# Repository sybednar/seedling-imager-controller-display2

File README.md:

# Seedling Imager Controller

## Overview
Inspired by the SPIRO (Smart Plate Imaging Robot; Ohlsson et al The Plant Journal doi: 10.1111/tpj.16587) project, the **Seedling Imager** is a Raspberry Pi 5-based imaging system designed to monitor Arabidopsis seedling growth using a 6-position hexagonal carousel. It provides automated imaging, LED control, and experiment scheduling through a touch-friendly GUI.

# Seedling Imager Controller — Universal

**v1.3.0** · Raspberry Pi 5 · PySide6 · picamera2 (or Arducam USB3) · GT2 belt carousel

A touchscreen controller for automated timelapse imaging of seedling plates using near-infrared (940 nm) transmission and front illumination. A single codebase runs on both supported display configurations without any code changes.

Repository: **https://github.com/sybednar/seedling-imager-controller-display2**

---

## Supported Hardware

| Component | System 1 (original) | System 2 |
|---|---|---|
| Display | Original 800×480 DSI touchscreen | Raspberry Pi Touch Display 2 (1280×720) |
| Scale factor `s` | 1.0 | 1.6 |
| Camera | Raspberry Pi HQ Camera | Raspberry Pi HQ Camera |
| Compute | Raspberry Pi 5 | Raspberry Pi 5 |
| Motor | Stepper + GT2 belt carousel | Stepper + GT2 belt carousel |
| Illumination | Dual 940 nm IR LEDs (front + rear) | Dual 940 nm IR LEDs (front + rear) |
| Optical sensor | Photointerrupter (hall + flag) | Photointerrupter (hall + flag) |
| Power (Pi 5) | SZZCNOX 5V/5A PD step-down module | SZZCNOX 5V/5A PD step-down module |

GUI layout, font sizes, button heights, and dialog dimensions all auto-scale via `s = screen_width / 800`. No separate display-specific files are needed.

> **Power supply note:** both systems use the same SZZCNOX 5V/5A USB-PD step-down board. A different-brand step-down module was tried on System 2 during a hardware upgrade and measured **5.42 V** on the Pi 5's 5V rail (GPIO pins 2/4) instead of 5.0 V — that ~0.2 V overvoltage is the confirmed cause of an intermittent shutdown/reboot hang (`plymouth-poweroff`/`plymouth-reboot` stuck for 1–2 minutes, or indefinitely). Swapping back to the SZZCNOX module resolved it completely. **Measure your 5V rail voltage before troubleshooting any shutdown/reboot instability in software** — it will look exactly like an OS or application bug otherwise. See Troubleshooting below.

---

## Key Features (v1.1.0)

### GUI & Display
- Auto-scaling dark theme UI: `s = screen_width / 800` (1.0 at 800 px, 1.6 at 1280 px)
- Fullscreen kiosk mode; all widget dimensions computed as `int(X * s)`
- `dark_style(s)` parameterized stylesheet — font, padding, and border-radius all scale

### Imaging
- Dual 940 nm IR illumination modes: **Front IR**, **Rear IR (transmission)**, **Combined**
- Per-mode camera presets stored in `camera_settings.json` (`FrontIR_*` / `RearIR_*` keys)
- Manual focus locked via `set_manual_focus()` at camera start (measured per unit — see Calibration Notes)
  - PDAF non-functional through 940 nm bandpass filter; manual focus required
- 16-bit grayscale TIFF output (`tifffile`; OpenCV fallback for non-TIFF formats)
- AE stability gate: polls `AnalogueGain` until < 5% relative change over 5 consecutive reads before pinning exposure
- `settling_started` signal emitted **after** AE is pinned and 0.20 s settle — GUI preview snapshot matches saved image exposure
- Live-view IR boost (mode-specific gain/exposure floor) enabled during preview, disabled before capture

### Motor / Carousel
- GT2 belt drive with dynamic bracket homing:
  1. CCW to LOW (leading edge of optical flag)
  2. CCW to HIGH (past leading edge)
  3. CW to LOW (re-validate leading edge)
  4. CW + `mid` µsteps to geometric center
- **Microstepping: 1/32** (BTT TMC2209: MS2=GND, MS1=VCC_IO). `steps_per_60_deg = 3200`.
  - This replaces the earlier 1/8-microstepping configuration (`steps_per_60_deg = 800`). 1/32 microstepping gives substantially finer positioning resolution and improved plate-to-plate registration — see Version History below.
  - **If you are upgrading an existing unit from a lower microstepping setting, delete `motion_cal.json` before the first run** — the saved calibration values do not scale automatically.
- Optical window `W` measured physically each homing run by counting µsteps CW across the sensor aperture (expected W ≈ 192 µsteps at 1/32 microstepping for the 5 mm stripe)
  - W is **not** a configurable parameter — it is measured live every homing cycle
- `CENTER_BACKOFF_FRAC = 0.0`: places carousel at exact geometric center regardless of W
  - Formula: `mid = max(1, int(round(W / 2.0 * (1.0 - CENTER_BACKOFF_FRAC))))`
  - Increase slightly (e.g. 0.05) only if consistent leading-edge drift is observed
- Log output includes `frac=` and `W=` on every homing for traceability

### Camera Backend (Picamera2 / Arducam USB3)
- Selectable in Camera Config → General tab: **Raspberry Pi Camera Module 3 (Picamera2)** [default] or **Arducam 20MP AR2020 Mono USB3**
- Persisted as `CameraBackend` in `camera_settings.json`; **switching requires an application restart** — the backend is fixed for the lifetime of the running process (`camera.py` only imports the selected backend module, since each one claims its physical camera device at import time)
- `camera.py` is a thin dispatcher: every other module calls `camera.get_frame()`, `camera.save_image()`, etc. unchanged regardless of which backend is active
- Arducam backend validated on physical hardware (Sept 2026): full-resolution reopen/discard/retry sequence confirmed reliable across extended multi-cycle experiments, including a `mock_capture()` path that exercises the same reopen sequence for unselected plates so every plate position gets a fresh, reliable on-screen preview whether or not it is actually captured that cycle. Before relying on it for a new unit:
  1. `sudo apt install v4l-utils` (already included in `install_dependencies.sh`)
  2. Connect the camera, then run `python3 -c "import camera_arducam_usb3 as c; c.print_diagnostics()"` — reports the detected `/dev/videoN` device, every resolution/format the driver advertises, and every V4L2 control it exposes
  3. Compare against the assumptions documented at the top of `camera_arducam_usb3.py` (control names, resolutions, mode-switch timing) and adjust the constants there if they don't match
- The Arducam is a **fixed physical manual-focus lens** (twist the M12 ring by hand) — there is no AF motor, so `set_manual_focus()`/AF-related calls are safe no-ops on this backend; the Focus tab in Camera Config has no effect when Arducam is selected
- UVC cameras generally stream one resolution at a time, unlike Picamera2's simultaneous main+lores streams — the Arducam backend runs live preview at a lower resolution continuously and briefly reconfigures to full resolution for each saved image (or each mock capture), so expect a short pause per cycle that the Picamera2 backend does not have

### Germination / Photomorphogenesis LEDs
- Independent on/off toggle buttons for **Blue (450 nm)**, **Red (660 nm)**, and **FarRed (730 nm)** — driven low-side via 3× IRLZ44N MOSFETs on the auxiliary MOSFET board
- Not coupled to the IR imaging illumination cycle — hold any combination on (e.g. Red+FarRed for a red:far-red ratio treatment) while IR imaging continues independently
- State is not persisted between sessions — all three channels default OFF at startup

### Camera Config Dialog
- Tabbed interface: General settings (incl. Camera Backend selector) + Focus + IR-specific presets
- "White LED Front" toggle button (GPIO23, persistent button row next to Apply/Close, not inside the Focus tab so it stays usable for either camera backend) — illuminates a Siemens star target during manual focus calibration; automatically turns off when the dialog closes (Close button, window X, or Escape key)
- Non-blocking "Read Current Position from Camera" button — `_FocusReader(QThread)` worker prevents GUI freeze when Live View is off
- Button disabled during read, re-enabled on completion or error

### Experiment Setup
- Configurable plate selection, frequency (default 30 min), duration, illumination mode
- Disk usage estimate uses `IMAGES_ROOT = Path("/home/sybednar/Seedling_Imager/images")` — **this path is hardcoded in `experiment_setup.py`.** If you use a different Linux username or folder layout, you must edit this line (see Setup, Step 0).
- Storage label colour: green (sufficient free space) / red (insufficient)

### File Manager
- Thumbnail grid with per-image metadata overlay
- Scaled thumbnail size: `QSize(int(100 * s), int(100 * s))`

---

## Module Structure

```
Seedling_Imager/                          # top-level project folder (NOT the git repo)
├── images/                               # timelapse output — IMAGES_ROOT (hardcoded path)
└── seedling_imager_controller/           # git clone of this repository
    ├── venv/                             # Python virtual environment (created locally, not in git)
    ├── main.py                           # Entry point; launches QApplication fullscreen
    ├── gui.py                            # Main window; computes s = screen_width / 800
    ├── styles.py                         # dark_style(s) — parameterized stylesheet
    ├── camera.py                         # Camera BACKEND DISPATCHER — selects picamera2 vs arducam_usb3
    ├── camera_picamera2.py               # Picamera2 backend; manual focus; TIFF save; AE gate
    ├── camera_arducam_usb3.py            # Arducam 20MP AR2020 mono USB3 backend (OpenCV/V4L2)
    ├── camera_config.py                  # Camera Config dialog; Camera Backend selector; _FocusReader QThread
    ├── motor_control.py                  # Stepper driver; dynamic bracket homing; 1/32 microstepping
    ├── experiment_runner.py              # Timelapse loop; AE settle; settling_started signal
    ├── experiment_setup.py               # Setup dialog; plate/frequency/mode/disk usage
    ├── file_manager.py                   # File browser with thumbnail grid
    ├── registration.py                   # Per-plate phase cross-correlation registration analysis
    ├── jog.py                            # Manual motor jog utility for bench testing
    ├── camera_settings.json              # Persisted camera presets (FrontIR_*, RearIR_* keys)
    ├── motion_cal.json                   # Persisted motor calibration (auto-created on first homing)
    ├── requirements.txt                  # pip dependencies (installed inside venv)
    ├── install_dependencies.sh           # One-shot apt + venv + pip installer
    ├── start_seedling_imager.sh          # Launch wrapper used by both autostart methods below
    ├── restart_seedling_imager.sh        # Manual stop/relaunch (used by desktop icon)
    ├── seedling-imager-autostart.desktop # XDG autostart template — RECOMMENDED (see Setup Step 8)
    ├── seedling-imager.service           # systemd --user service template — optional/alternative (see Setup Step 8)
    ├── Seedling_Imager.desktop           # Desktop icon template — start/restart the controller (see Setup Step 9)
    ├── git_update.sh                     # Convenience script for commit + tag + push
    ├── hardware/                         # CAD (STEP), KiCad boards, BOM, render, hardware licence — see hardware/README.md
    ├── logs/                             # Experiment run logs
    └── README.md
```

---

## GPIO Pin Map (as of v1.2.0)

All pins below are on the auxiliary MOSFET board or the motor driver, addressed via `gpiod` against `/dev/gpiochip0`.

| GPIO | Function | Module |
|---|---|---|
| 12 | Germination LED — Blue 450 nm | `gui.py` |
| 13 | Germination LED — Red 660 nm | `gui.py` |
| 16 | Motor DIR | `motor_control.py` |
| 17 | Front IR imaging panel (reflectance) | `gui.py` |
| 19 | Germination LED — FarRed 730 nm | `gui.py` |
| 20 | Motor STEP | `motor_control.py` |
| 21 | Motor driver EN | `motor_control.py` |
| 22 | Optical sensor (reflective stripe) | `motor_control.py` |
| 23 | Front panel White LED strip (Siemens star illumination during manual focus calibration) | `camera_config.py` |
| 24 | Green front illumination | `gui.py` |
| 26 | Hall sensor (motor pre-index) | `motor_control.py` |
| 27 | Rear IR imaging panel (transmission) | `gui.py` |

**v1.2.0 pin reshuffle:** `OPTICAL_PIN` moved 19→22 and the front/rear IR imaging panels moved 13→17 and 12→27, freeing GPIO12/13/19 for the three germination LED channels above. If you're carrying forward calibration or wiring notes from before v1.2.0, update them against this table, not the older pin numbers referenced in earlier Version History entries.

---

## Dependencies

Installed as **apt system packages** (compiled against Raspberry Pi OS's libcamera/Qt6/GPU libraries — do not pip-install these):
```
python3-picamera2
python3-pyside6.*    (no single "python3-pyside6" metapackage on current Raspberry Pi OS/Debian
                       Trixie — PySide6 is split per Qt module; the wildcard installs all of them:
                       sudo apt install 'python3-pyside6.*')
python3-numpy
python3-opencv      (cv2)
v4l-utils           (provides v4l2-ctl — only needed if using the Arducam USB3 camera backend)
libxcb-cursor0      (required by Qt >= 6.5's xcb platform plugin; usually already present, but
                     confirmed missing on at least one fresh Raspberry Pi OS Trixie image — see
                     Troubleshooting)
```

Installed as **pip packages inside the project virtual environment** (see `requirements.txt`):
```
tifffile   (16-bit TIFF read/write)
gpiod>=2.0 (stepper/LED GPIO — modern gpiod.line API; see https://pypi.org/project/gpiod/)
```

> **Note on GPIO library:** this project uses `gpiod` (the modern libgpiod v2.x Python bindings), **not** `RPi.GPIO` and **not** `gpiozero`. Both are absent from the codebase. `gpiod` is installed via pip (not apt) because the apt-packaged `python3-libgpiod` on current Raspberry Pi OS releases may ship an older 1.x API incompatible with `motor_control.py`'s `gpiod.line.Direction/Value/Bias` usage.

The `install_dependencies.sh` script (see Setup below) installs and verifies all of the above in one step.

---

## Setup — New Raspberry Pi 5 (Step by Step for Novices)

These instructions assume you have already flashed Raspberry Pi OS (Bookworm or Trixie) onto the NVMe/SD card, booted to the desktop, confirmed **Desktop Autologin** is enabled for your user (`sudo raspi-config` → System Options → Boot / Autologin → Desktop Autologin), and connected to Wi-Fi/Ethernet. All commands are run in a terminal on the Raspberry Pi itself (or over SSH — except where noted in Step 8/9, where a few things must be checked from a terminal running *inside* the desktop session itself).

### Step 0 — Confirm your Linux username

The code hardcodes the path `/home/sybednar/Seedling_Imager/...` in two places (`experiment_setup.py`'s `IMAGES_ROOT`, and the autostart scripts). Open a terminal and run:

```bash
whoami
```

- If it prints `sybednar`, continue to Step 1 as written.
- If it prints anything else, either (a) create a `sybednar` user on this Pi, or (b) do a project-wide find-and-replace of `/home/sybednar/` with `/home/<your-username>/` in `experiment_setup.py`, `start_seedling_imager.sh`, `restart_seedling_imager.sh`, `seedling-imager.service`, and `seedling-imager-autostart.desktop` before proceeding.

### Step 1 — Create the project folder

```bash
mkdir -p /home/sybednar/Seedling_Imager/images
cd /home/sybednar/Seedling_Imager
```

### Step 2 — Clone the repository

```bash
git clone https://github.com/sybednar/seedling-imager-controller-display2.git seedling_imager_controller
cd seedling_imager_controller
```

(HTTPS clone requires no GitHub account or SSH key setup — fine for read-only cloning of this public repo. If you need the Arducam USB3 branch specifically, add `-b arducam-integration` to the clone command.)

### Step 3 — Install dependencies (one command)

```bash
chmod +x install_dependencies.sh
./install_dependencies.sh
```

This installs the apt system packages, creates `venv/` with `--system-site-packages`, installs `requirements.txt` into it, and prints a verification check for every dependency (picamera2, PySide6, opencv, numpy, tifffile, gpiod). **Do not continue to Step 4 until this script finishes with no errors.**

### Step 4 — Make the launch/restart scripts executable

```bash
chmod +x start_seedling_imager.sh restart_seedling_imager.sh
```

### Step 5 — First manual run (before enabling autostart)

Always test manually first — it's much easier to read errors in a live terminal than in a log file. Run this from a terminal opened **on the Pi's own desktop** (not a bare SSH session), since the app needs the desktop's live display/session environment:

```bash
source venv/bin/activate
python3 main.py
```

The app should open fullscreen. Use Alt+F4 (or the on-screen Exit control, if present) to close it and return to the terminal. If it fails to start, see Troubleshooting below before continuing.

### Step 6 — Calibrate manual focus for this camera unit

Manual focus is **per-camera-unit** and must be re-measured on every new Pi/camera pairing — do not reuse another unit's value. Follow the steps in the repository's `Setting manual camera focus instructions` file, then update the `ManualFocusPosition` value(s) in `camera_settings.json`.

### Step 7 — Confirm the motor calibration file is fresh

If this SSD/OS image was ever used with a different microstepping setting or a different physical unit, delete the stale calibration before the first homing run:

```bash
rm -f /home/sybednar/Seedling_Imager/seedling_imager_controller/motion_cal.json
```

It will be recreated automatically the first time `home()` runs successfully from the GUI.

### Step 8 — Enable autostart (XDG autostart, recommended)

Two mechanisms exist for autostarting the controller GUI when the desktop session starts: a **systemd `--user` service** and an **XDG autostart `.desktop` entry**. Real-world testing across two different Pi 5 units (and, on one of them, two different OS images) consistently found the systemd method **unreliable for this application**: it works fine when started by hand in an already-running session (`systemctl --user enable --now ...`), but on a genuine cold `sudo reboot` it either fails with a Qt platform-plugin error or exits silently a few seconds after launch, with no window ever appearing. The confirmed root cause is that the systemd user manager on these Pi 5 / labwc images does not reliably import `XAUTHORITY`/`WLR_XWAYLAND` into its environment the way an interactive desktop session does — `DISPLAY` and `WAYLAND_DISPLAY` are present, but the xcb/XWayland platform plugin still can't authenticate without those two extra variables. `start_seedling_imager.sh` already sets explicit fallback defaults for both (see the script), which helps but has not made systemd fully reliable across every image tested. The **XDG autostart** method sidesteps the problem entirely, since the compositor launches it directly inside the already-fully-initialized session — it has been 100% reliable across every reboot/shutdown test performed. **Use it as the primary method:**

```bash
mkdir -p ~/.config/autostart
cp seedling-imager-autostart.desktop ~/.config/autostart/seedling-imager.desktop
```

**Reboot the Pi with `sudo reboot` (a real reboot — not `systemctl --user start`) and confirm the controller launches automatically to the fullscreen GUI.** Also test a full `sudo shutdown now` to confirm the Pi actually powers off cleanly. Testing only with a live-session start can look successful and still fail on a real cold boot — always validate with an actual reboot and an actual shutdown before considering autostart done.

If the GUI doesn't appear, check the log first:

```bash
tail -80 /home/sybednar/Seedling_Imager/seedling_imager_controller/autostart.log
```

<details>
<summary>Optional: systemd <code>--user</code> service (alternative method — click to expand)</summary>

If you'd prefer process supervision (automatic restart on crash) and are willing to validate it carefully, the systemd unit is still provided:

```bash
mkdir -p ~/.config/systemd/user
cp seedling-imager.service ~/.config/systemd/user/
systemctl --user daemon-reload
systemctl --user enable --now seedling-imager.service
```

Check it's running:

```bash
systemctl --user status seedling-imager.service --no-pager -l
```

**Do not stop here** — this only confirms it works when started inside your current live session, which is exactly the false-positive result seen on both test units before a real reboot exposed the failure. Reboot and re-check status/log before trusting it:

```bash
sudo reboot
# after it comes back up:
systemctl --user status seedling-imager.service --no-pager -l
tail -80 /home/sybednar/Seedling_Imager/seedling_imager_controller/autostart.log
```

If it fails (Qt platform-plugin error, or the log shows the script exiting cleanly within a few seconds of launch with no other error), fall back to the XDG method above:

```bash
systemctl --user disable --now seedling-imager.service
mkdir -p ~/.config/autostart
cp seedling-imager-autostart.desktop ~/.config/autostart/seedling-imager.desktop
sudo reboot
```

</details>

### Step 9 — Add the "Seedling Imager" desktop icon

This lets you start (or stop-and-relaunch) the controller from the touchscreen — e.g. after using "Exit to Desktop" to review files — without rebooting the Pi.

```bash
cp Seedling_Imager.desktop ~/Desktop/
chmod +x ~/Desktop/Seedling_Imager.desktop
```

**Two one-time desktop settings, or the icon won't work smoothly:**

1. On first double-click, the file manager may show an "Untrusted application launcher" warning — right-click the icon and choose **Allow Launching** (or **Trust**), then it will run normally from then on.
2. By default, clicking an executable `.desktop`/script icon pops up an "Execute / Execute in Terminal / Display / Cancel" dialog every time instead of just running it. To disable this: open the **File Manager**, go to **Edit → Preferences** (or right-click the desktop → **Desktop Preferences**, depending on OS version), find the **General** tab, and check **"Don't ask options on launch executable file."** Without this, every click on the icon interrupts the user with an extra dialog.

The icon uses `seedlings.png` (already in this repo) and calls `restart_seedling_imager.sh`, which kills any already-running instance of the GUI and relaunches `start_seedling_imager.sh` fresh — safe to click whether or not the controller is currently running.

### Step 10 — Run a short registration test

Run a short multi-cycle experiment (a few plates, a few cycles) and inspect results with `registration.py` to confirm the 1/32-microstepping `motor_control.py` gives the same registration improvement seen on System 1 before starting a long unattended run.

---

## Troubleshooting

| Symptom | Likely cause / fix |
|---|---|
| `pip install` fails with "externally-managed-environment" | You're not inside the venv, or the venv was created without `--system-site-packages`. Re-run `source venv/bin/activate` first, or rebuild the venv per Step 3. |
| `ModuleNotFoundError: No module named 'picamera2'` inside the venv | The venv wasn't created with `--system-site-packages`, or the apt package `python3-picamera2` isn't installed. Rebuild: `rm -rf venv && python3 -m venv --system-site-packages venv`, then re-run `install_dependencies.sh`. |
| `ImportError: cannot import name 'Direction' from 'gpiod.line'` | An old `gpiod` (1.x) is shadowing the pip-installed 2.x version. Confirm with `venv/bin/pip show gpiod` (should be ≥2.0) and re-run `venv/bin/pip install --upgrade gpiod`. |
| `qt.qpa.plugin: Could not load the Qt platform plugin "xcb" ... xcb-cursor0 or libxcb-cursor0 is needed` | Missing system library required by Qt ≥ 6.5. Fix: `sudo apt-get install -y libxcb-cursor0`. Seen on a fresh Raspberry Pi OS Trixie image where it wasn't pulled in automatically. |
| `qt.qpa.xcb: could not connect to display` when testing manually | You're running the command over plain SSH (no `DISPLAY`), not in a terminal inside the desktop session. Either open a terminal locally on the Pi's touchscreen, or (for a quick manual check only) `export DISPLAY=:0` in the SSH shell first. |
| GUI never appears at boot, but manual `python3 main.py` (run inside the desktop session) works fine | This is the systemd `XAUTHORITY`/`WLR_XWAYLAND` gap described in Setup Step 8. Switch to the XDG autostart method — don't spend time tuning `QT_QPA_PLATFORM` or startup delay first, since neither addresses the actual cause. |
| systemd service shows `enabled`, `autostart.log` shows the script reach `Seedling Imager launch end` a few seconds after launch, but no window ever appeared | The app started and exited cleanly on its own under systemd — a different, not-fully-understood failure mode from the Qt platform-plugin error above, also resolved by switching to XDG autostart. Confirmed independent of camera backend and hardware revision. |
| systemd service works when started by hand (`enable --now`) but not after a real `sudo reboot` | Expected — see Setup Step 8. Validate autostart only with a genuine reboot, never with a live-session start. |
| `sudo shutdown`/`sudo reboot` hangs for 1–2 minutes (or indefinitely) at a `plymouth-poweroff`/`plymouth-reboot` message | Check your Pi 5's 5V rail voltage (GPIO pins 2/4) before assuming it's a software issue — a step-down power module running even slightly over 5.0 V (5.4 V confirmed to cause this) can produce exactly this symptom. See the Power Supply note near the top of this README. Also run `sudo rpi-eeprom-update` and apply any pending bootloader update (`sudo rpi-eeprom-update -a && sudo reboot`) as a secondary check, especially on units with an NVMe HAT. A momentary pushbutton wired to the J2 GPIO shutdown pins will reliably force a clean power-down while you diagnose this. |
| Clicking the desktop icon pops up an Execute/Terminal/Cancel dialog every time | See Setup Step 9 — enable "Don't ask options on launch executable file" in the File Manager's preferences. |
| Homing/centering seems off after this update | Delete `motion_cal.json` and re-home — old calibration values from a different microstepping setting do not carry over (see Motor / Carousel notes above). |

---

## Migrating an Existing Unit to This Layout

If a unit's folder/autostart layout predates this document, bringing it in line is usually a small job, not a rebuild:

1. **Confirm the folder structure first before assuming anything needs to move.** Check `ls -la /home/<user>/Seedling_Imager/` and `ls -la /home/<user>/Seedling_Imager/seedling_imager_controller/venv/bin/python3` — many units already have the correct layout (repo cloned into `Seedling_Imager/seedling_imager_controller/`, venv nested inside it) even if that wasn't true at some earlier point in the unit's history. Don't move files that are already in the right place.
2. **The autostart mechanism is the part most likely to need changing.** If the unit currently relies on the systemd `--user` service, convert it to the XDG autostart method per Setup Step 8 — do this even if the systemd version currently "seems to work," since a live-session start can pass while a real cold reboot fails (see Troubleshooting). Validate with an actual `sudo reboot` and `sudo shutdown`, not just `systemctl --user enable --now`.
3. Update the desktop icon to the current `Seedling_Imager.desktop` template and confirm the File Manager preference from Setup Step 9 is set.
4. Back up (rename, don't delete) any old/stale project folders before removing them, and only delete the backups once the converted unit has been confirmed working across a real reboot and shutdown.
5. **Do not touch a unit while it is running an experiment.** Do this migration between experimental runs.

---

## Calibration Notes

### Manual Focus
- Manual focus is per-camera-unit. Measure and set `ManualFocusPosition` in `camera_settings.json` for each new system — do not copy another system's value.
- PDAF is non-functional through the 940 nm bandpass filter on both systems.

### Optical Window W
W is measured automatically on every homing cycle — no manual configuration needed. Expect W ≈ 192 µsteps at 1/32 microstepping for the 5 mm stripe.

### CENTER_BACKOFF_FRAC
At the top of `motor_control.py`. Default `0.0` places the carousel at exact geometric window center. Only increase if consistent leading-edge drift is observed in registration analysis.

---

## Hardware Design Files

The complete open-source hardware design is in [`hardware/`](hardware/README.md): the full assembly and individual parts in STEP format, KiCad 10 schematics and PCB layouts for the controller boards and hall sensor board, and a bill of materials (`hardware/CAD Files/bill_of_materials.md`). The native Fusion archive (`.f3z`) and full-assembly STEP are too large for the repository and are attached to the [latest GitHub Release](https://github.com/sybednar/seedling-imager-controller-display2/releases/latest). Hardware files are licensed under CERN-OHL-S v2; the software is MIT.

---

## Version History

### v1.3.2 — 2026-10-04 — Hardware documentation and naming corrections

- Renamed the IR filter holder component to "850 nm long-pass filter holder" in the CAD (Fusion archive and all STEP files)
- Clarified that the camera housing, filter holder and rail corner bracket are included in the Picamera mount STEP; updated root README, CHANGELOG and citation
- Software unchanged from v1.3.0

### v1.3.1 — 2026-10-04 — Complete hardware design files

- Added the complete hardware design (`hardware/`): full-assembly STEP (zipped) and individual part STEP files by subsystem, KiCad 10 files for controller board 1, board 2 and the hall sensor board, bill of materials, assembly render, and CERN-OHL-S v2 licence/notice
- Fusion archive (`.f3z`) and full-assembly STEP attached to the GitHub Release (files exceed GitHub's 100 MB repository limit)
- Added root `LICENSE` (MIT) for the software
- Software unchanged from v1.3.0

### v1.3.0 — 2026-09-27 — Arducam reliability fixes, White LED Front control, Picamera2 for production

**Reliability fixes**
- Fixed `focus_tune.py` sharpness score: removed per-frame min/max contrast normalization that was causing the reported score to rise with *increasing* defocus instead of decreasing
- Fixed Arducam USB3 single-capture failure (root-caused via `dmesg`: `uvcvideo: Failed to resubmit video URB`, a genuine kernel-level USB/firmware wedge triggered by rapid full-res/preview mode switching) — added a settle delay before reopening the device plus self-healing device re-detection (`_find_device(force_refresh=True)`)

**New hardware control**
- Added a "White LED Front" toggle button (GPIO23) to the Camera Config dialog, placed in the persistent button row so it stays usable regardless of active tab or selected backend. Illuminates a Siemens star target for manual focus calibration on either camera; auto-shuts-off via the dialog's `finished` signal so it turns off no matter how the dialog is closed
- Corrected GPIO Pin Map: GPIO23 and GPIO24 were previously documented as "reserved, not yet implemented" — GPIO24 was already driving the Green front illumination LED (`gui.py`), and GPIO23 now drives the White LED Front strip above, both via the AO4805 MOSFET auxiliary board

**Hardware/production decision**
- Head-to-head image-quality comparison on both systems (focus, depth of field, sharpness) showed Picamera2/Camera Module 3 substantially outperforming the Arducam 20MP AR2020 Mono + AICO M12 lens combination for real seedling-plate imaging, after root-causing the Arducam's low sharpness ceiling to a Minimum-Object-Distance violation (measured working distance below the lens's MOD). Both systems switched to Picamera2 for production experiments; the Arducam lens/working-distance problem is tabled for future revisit — the backend and its fixes above remain in the codebase and selectable via Camera Config

**Repo maintenance**
- Consolidated system 1 onto `origin/main`, resolving stale branch/merge-conflict history
- Fixed GitHub default branch (was pointing to the archived `archive-pre-arducam-2026-04` branch instead of `main`); deleted stale `arducam-integration` and `archive-pre-arducam-2026-04` branches and the leftover local `main-old-stale`

### v1.2.1 — 2026-09 — Autostart reliability fix + setup documentation overhaul

**Autostart**
- Root-caused systemd `--user` autostart unreliability to `XAUTHORITY`/`WLR_XWAYLAND` not being reliably imported into the systemd user manager's environment on Pi 5/labwc images, even though `DISPLAY`/`WAYLAND_DISPLAY` are present. `start_seedling_imager.sh` now sets explicit fallback defaults for both.
- XDG autostart (`~/.config/autostart/`) promoted to the **recommended** primary method after passing repeated real cold-reboot and full-shutdown testing on two separate physical units; systemd retained as a documented, secondary/optional method.
- Desktop icon renamed/consolidated to a single `Seedling_Imager.desktop` template (start-or-restart), replacing the earlier restart-only icon naming.

**Hardware**
- Documented a confirmed root cause for intermittent `plymouth-poweroff`/`plymouth-reboot` shutdown hangs: a non-matching 5V step-down power module running at 5.42 V instead of 5.0 V. Resolved by standardizing on the SZZCNOX 5V/5A module on both systems.
- Added `sudo rpi-eeprom-update` as a secondary shutdown-instability check, particularly for units with an NVMe HAT.

**Camera**
- Arducam USB3 backend validated against physical hardware across extended multi-cycle runs; added `mock_capture()` so every plate position gets a fresh, reliable on-screen preview regardless of whether that plate is actually captured that cycle.

**Dependencies**
- Added `libxcb-cursor0` as a documented apt dependency (Qt ≥ 6.5 requirement, found missing on a fresh Raspberry Pi OS Trixie image).

### v1.2.0 — 2026-08 — Selectable camera backend, germination LEDs, GPIO reshuffle

**Camera**
- `camera.py` split into a backend dispatcher plus two implementations: `camera_picamera2.py` (existing Picamera2/libcamera code, behavior unchanged) and new `camera_arducam_usb3.py` (OpenCV/V4L2 backend for the Arducam 20MP AR2020 monochrome USB3 camera)
- Backend selectable in Camera Config → General (`CameraBackend` in `camera_settings.json`); requires an app restart to take effect

**Hardware / GPIO**
- Added a 3-channel germination/photomorphogenesis LED strip (Blue 450 nm, Red 660 nm, FarRed 730 nm) with independent GUI on/off toggles, driven low-side via IRLZ44N MOSFETs on a new auxiliary MOSFET board
- Reshuffled GPIO pins to make room: `motor_control.py`'s `OPTICAL_PIN` moved 19→22; `gui.py`'s front/rear IR imaging panel pins moved 13→17 and 12→27. See the GPIO Pin Map above for the full current assignment, including GPIO23/24 reserved for a planned rear-IR940 PWM intensity control (AO4805 mosfet, not yet implemented in software)

**Dependencies**
- Added `v4l-utils` (apt) for the Arducam backend's `v4l2-ctl`-based exposure/gain control

### v1.1.0 — 2026-07 — 1/32 microstepping + documentation overhaul

**Motor**
- `motor_control.py` updated from 1/8 to 1/32 microstepping (`steps_per_60_deg`: 800 → 3200), same single-optical-sensor + 6-stripe dynamic-bracket strategy. Finer step resolution further improves plate-to-plate registration.
- Cleaned a leftover dead-code block in `_debounced_read()`.

**Documentation**
- Corrected GPIO dependency: `RPi.GPIO`/`gpiozero` (never used in code) replaced with `gpiod>=2.0` throughout.
- Replaced three conflicting clone/folder-structure instructions with a single canonical layout and step-by-step novice setup guide.
- Added `requirements.txt`, `install_dependencies.sh`, systemd service template, XDG autostart fallback template, and desktop restart-icon template — previously undocumented/uncommitted.
- Fixed repository URL (previous README referenced two nonexistent repo names).

### v1.0.0 — 2026-04-22 — Universal release

**Architecture**
- Single codebase runs on both 800×480 and 1280×720 displays without modification
- `s = screen_width / 800` computed once in `gui.py`; every pixel dimension expressed as `int(X * s)`
- `dark_style(s)` replaces fixed stylesheet string; font, padding, border-radius all scale with `s`

**Motor / centering fix**
- `CENTER_BACKOFF_FRAC = 0.0` replaces fixed `CENTER_BACKOFF = 5`
- Fixes System 1 centering error: with W=12 the old formula gave `mid=1` (leading edge) instead of `mid=6` (center)
- After pulley realignment: W=23–24, mid=12; registration RMS improved ~79% (6.7 px → 1.4 px mean)

**Imaging**
- AE stability gate: waits for AnalogueGain < 5% relative change × 5 consecutive reads before pinning exposure
- `settling_started` signal timing fixed: now emitted after AE pin + 0.20 s settle, not before — preview snapshot matches saved image exposure
- Non-blocking Read Focus button: `_FocusReader(QThread)` prevents GUI freeze when Live View is off

**Bug fixes**
- `IMAGES_ROOT` constant added to `experiment_setup.py` (was causing silent disk estimate failure)
- Experiment frequency default restored to 30 minutes
- `apply_main_illum_style` scope fix: `s = self._s` added inside method body
- `experiment_setup.py` line 235: orphaned `else` clause fixed (comment had been inserted between `if` body and `else`)
- `gui.py`: `setStyleSheet(dark_style(s))` moved to after `s` is computed (was causing `UnboundLocalError`)

**All v0.06 Display2 features carried forward**
- Dual 940 nm IR illumination (front + rear), per-mode camera presets
- Tabbed Camera Config dialog, File Manager with thumbnails, CSV metadata
- GT2 belt drive, autostart and desktop launcher

### v0.06 — Display2-specific release
Dual-stream camera, TIFF output, autofocus, File Manager with thumbnails, CSV metadata, Camera Config dialog, autostart and desktop launcher, GT2 belt drive initial implementation, per-mode IR presets.

---

## Registration Performance (System 1, v1.0.0, 1/8 microstepping baseline)

Rear IR transmission, 8 cycles, plates 1 and 2:

| Metric | v0.06 baseline | v1.0.0 |
|---|---|---|
| Mean RMS | 6.7 px | 1.4 px |
| Mean \|dx\| | 6.5 px | 1.3 px |
| dx bias | +6.5 px (systematic) | −0.4 px (eliminated) |
| Cycles at 0 px shift | 0 of 4 | 9 of 14 (64%) |
| Max \|dx\| | 10 px | 6 px |

Residual jitter (2–6 px) is intrinsic GT2 belt backlash and stepper microstepping nonlinearity. Software registration using ArUco or QR fiducial markers on plate backs can correct remaining shift to sub-pixel if required for quantitative analysis. **1/32-microstepping results from System 2 will be added here once validated (see Setup Step 10).**

---

## License

Software: MIT — see `LICENSE` file. Hardware design files (`hardware/`): CERN-OHL-S v2 — see `hardware/LICENSE-CERN-OHL-S-v2.txt`.

Citation: Bednarek, S. Y., Yong, C. W. J., Hoey, E. A. and Murua, K. (2026). *seedling-imager-controller-display2* (v1.3.2). Zenodo. https://doi.org/10.5281/zenodo.23144486 (all versions: https://doi.org/10.5281/zenodo.20738657).

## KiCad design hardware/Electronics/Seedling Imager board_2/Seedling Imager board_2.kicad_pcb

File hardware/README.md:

# Seedling Imager — Hardware Design Files

Open-source hardware for an automated, six-plate time-lapse seedling imaging robot.
This folder contains the mechanical CAD files, controller electronics (KiCad), bill of
materials, and licensing for the imager; the Raspberry Pi controller and
image-acquisition/registration software live in the root of this repository.

## Overview

The instrument is a rotating hexagonal carousel that holds up to six Petri plates and
presents each in turn to a fixed high-resolution camera. It is controlled by a
Raspberry Pi with a stepper motor and optical/magnetic position sensors, so every plate
returns to the same imaging position on each cycle. Plates are illuminated with both
transmitted and reflected 940 nm infrared light, allowing seedlings to be grown and
imaged either in the light or in complete darkness (etiolated), typically at 1–2 hour
intervals over 5–7 days. The system captures 16-bit grayscale TIFF images and
automatically aligns successive frames of each plate by phase cross-correlation
(frame-to-frame registration to ~2 pixels in current data).

The design was inspired by the open-source SPIRO Petri-plate imaging robot
(Ohlsson et al., 2024, *The Plant Journal* 118:584–600) and extends it with greater
plate capacity, dual transmitted + reflected IR illumination, and improved registration
reproducibility for quantitative time-lapse growth analysis.

## Contents

| Path | Description |
|------|-------------|
| `seedling imager_full assembly.step.zip` | Complete assembly in neutral STEP format (zipped; unzip before opening). Opens in any CAD package (FreeCAD, SolidWorks, Onshape, etc.). |
| Fusion archive `seedling imager_full assembly.f3z` | Native Autodesk Fusion archive of the complete assembly (127 MB, too large for the repository). Download from the **[latest GitHub Release](https://github.com/sybednar/seedling-imager-controller-display2/releases/latest)** and open in Fusion. |
| `CAD Files/` | Individual part and sub-assembly STEP files, organized by subsystem (below), plus `bill_of_materials.md`. |
| `Electronics/` | KiCad 10 schematic and PCB design files for the controller boards and hall sensor board (below). |
| `LICENSE-CERN-OHL-S-v2.txt` | Hardware license (see Licensing). |
| `NOTICE.txt` | Required CERN-OHL-S copyright/license notice. |

### CAD Files/ (STEP format, by subsystem)

| Folder | Contents |
|--------|----------|
| `Drive Base and Frame/` | Base plate, top plate, motor tensioning plate |
| `Carousel Assembly/` | Six-plate carousel with dual-bearing belt drive, carousel support bracket, adjustable bearing arms (including the optical sensor mount and the hall sensor arm), acrylic plate diffuser, the dual bearing belt drive motor base block, and the magnet and optical carousel position sensor triggers |
| `Rear Illuminator/` | Rear IR/illumination support hub |
| `Camera and Controller Mount/` | Display/camera rail light screen mounting hub assembly; Picamera mount with CSI-to-HDMI board (includes the camera housing, IR long-pass filter holder and rail corner bracket) |
| `Controller Enclosure/` | Display/touchscreen controller enclosure assembly (hinge, touchscreen compartment, RPi compartment, rear panel) |
| `Controller Subassembly/` | 3D models of the custom controller boards (Seedling Imager board_1 and board_2) |
| `Miscellaneous Hardware/` | 2020 T-slot end cap with cover, 2020 T-slot cover wire guide, 2020 8 mm cable guide, 100 mm × 15 mm square Petri dish magnetic fastener (8 mm magnet), M5 thumb screws (15 mm and 25 mm), Meanwell LRS-100-12 power supply enclosure, corner bracket, and fabrication jigs (acrylic diffuser hole-drilling jig, spindle heat-set insert installation jig) |

Standard off-the-shelf hardware (fasteners, 2020 aluminum extrusion, stepper motor, etc.)
is not included as CAD files — see `CAD Files/bill_of_materials.md` for part numbers.

### Electronics/ (KiCad 10)

| Folder | Description |
|--------|-------------|
| `Seedling Imager board_1/` | Main controller board (TMC2209 stepper driver, LED and sensor interfaces). Includes the `TSW_103_07_L_S` library (symbol, footprint and 3D model for the 0.1" pitch header). |
| `Seedling Imager board_2/` | Auxiliary MOSFET board for LED illumination control. |
| `Seedling Imager hall sensor board/` | A3144 hall sensor board mounted in the adjustable bearing arm for magnetic carousel position sensing. |

Each folder holds the `.kicad_pro`, `.kicad_sch` and `.kicad_pcb` files; open the
`.kicad_pro` in KiCad 10 or later. Schematic symbols and PCB footprints are embedded in
the files, so the boards open without extra libraries. Some PCB files reference 3D
models by absolute path on the author's machine; these only affect the 3D viewer and can
be re-pointed in *PCB Editor ▸ Preferences ▸ Configure Paths* or by editing footprint
properties.

## Opening the design files

- **STEP (.step):** Unzip `seedling imager_full assembly.step.zip`, then open the `.step`
  in any CAD program. STEP preserves exact solid geometry and is the recommended
  starting point for reuse or modification outside Fusion. The individual `.step` files
  in `CAD Files/` can be opened directly.
- **Fusion archive (.f3z):** Download it from the latest GitHub Release, then in Autodesk Fusion use *File ▸ Open* and select the `.f3z`,
  or upload it to your Fusion data panel. This is the fully editable source design
  (Fusion is free for personal/hobbyist use).

## Bill of materials

See `CAD Files/bill_of_materials.md`, grouped by category (structural and motion
components, electronics, power, motor, lights, wiring, hardware, ArUco markers, 2020
extrusion cut list, camera housing hardware, and controller board connectors).

## Notes

- An alternate camera/lens configuration (Arducam 20 MP monochrome + Computar M0814-MP2
  C-mount lens) was evaluated but has not yet been built or tested. Its CAD files are not
  included; the Picamera system above is the one running production experiments.
- The camera housing/mount, the IR long-pass filter holder (for the 37 mm 850 nm filter) and the
  mounting rail corner bracket are modeled as components of
  `Camera and Controller Mount/picamera mount_with csi to hdmi board.step` (and of the full
  assembly) rather than as separate files.

## Build and operation

Controller setup, camera configuration, and operation: see the documentation in the
repository root (`README.md`, `Camera configuration_user guide`,
`Setting manual camera focus instructions`).

## Licensing

This project uses two licenses:

- **Hardware design files** (CAD, STEP, KiCad, BOM) in this folder are licensed under the
  **CERN Open Hardware Licence Version 2 — Strongly Reciprocal (CERN-OHL-S v2)**.
  See `LICENSE-CERN-OHL-S-v2.txt` and `NOTICE.txt`.
- **Software** (the Raspberry Pi controller and image-acquisition/registration code) in
  the repository root is licensed under the **MIT** license.
  See the `LICENSE` file at the repository root.

## Citation

If you use this hardware or software, please cite the archived release:

> Bednarek, S. Y., Yong, C. W. J., Hoey, E. A. and Murua, K. (2026). *seedling-imager-controller-display2: control and image-acquisition
> software and hardware design files for an open-source six-plate infrared seedling imaging
> robot* (v1.3.2) [Software and hardware design files]. Zenodo. https://doi.org/10.5281/zenodo.23144486
>
> The DOI above is for release v1.3.2. To cite all versions (always resolves to the latest
> release), use https://doi.org/10.5281/zenodo.20738657.

## Contact

Sebastian Y. Bednarek, University of Wisconsin–Madison — sybednar@wisc.edu

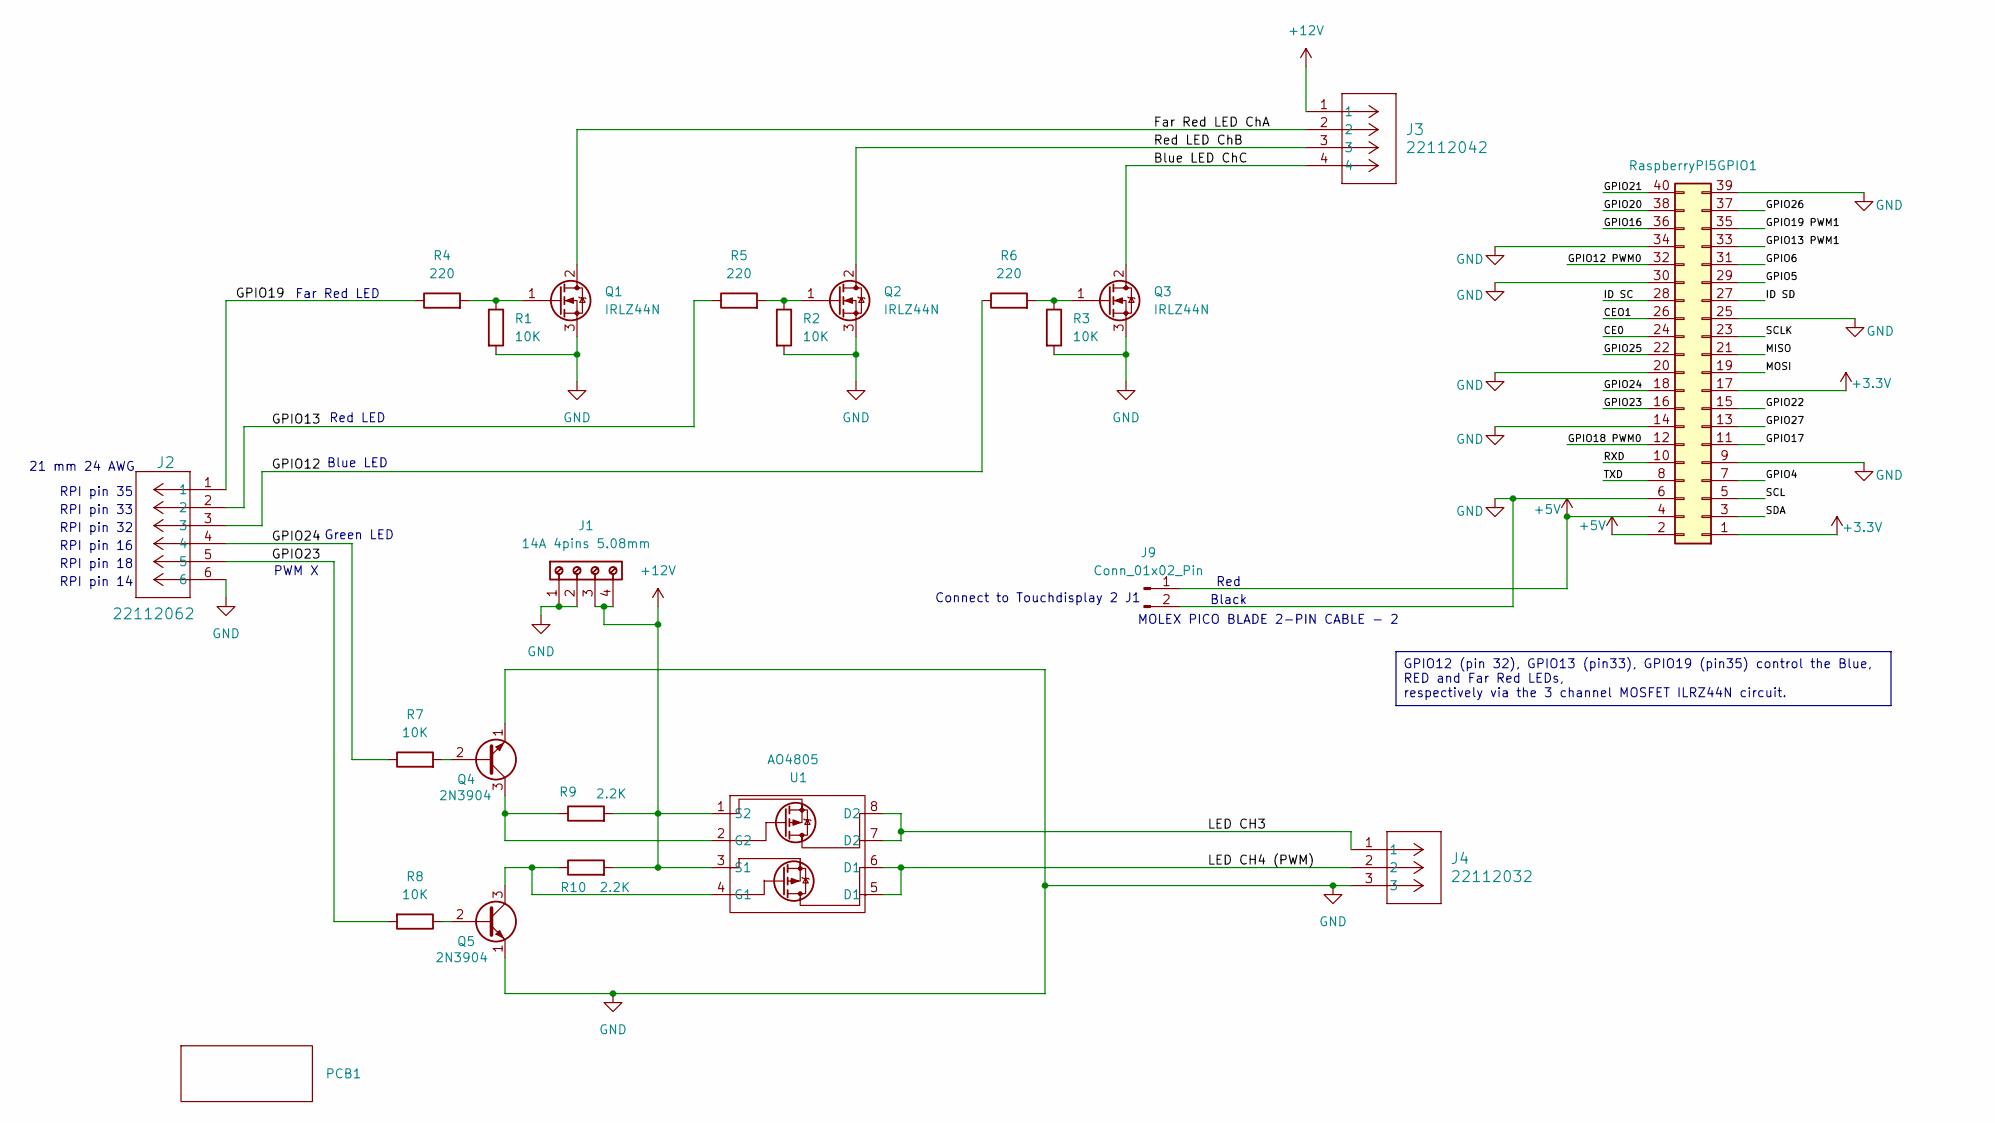
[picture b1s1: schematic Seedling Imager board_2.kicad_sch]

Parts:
J1: 691241510004; J_Wurth_WR-TBL_691241510004; Part Number 691241510004
J2: 22112062; CONN_A-6373-06A_MOL
J3: 22112042; CONN_A-6373-04A_MOL
J4: 22112032; CONN_A-6373-03A_MOL
J9: Conn_01x02_Pin
PCB1: DMB-4770-CB_cut
Q1, Q2, Q3: IRLZ44N; TO-220-3_Vertical
Q4, Q5: 2N3904; TO-92_Inline_Wide
R1, R2, R3, R7, R8: 10K; R_Axial_DIN0204_L3.6mm_D1.6mm_P5.08mm_Horizontal
R4, R5, R6: 220; R_Axial_DIN0204_L3.6mm_D1.6mm_P5.08mm_Horizontal
R9, R10: 2.2K; R_Axial_DIN0204_L3.6mm_D1.6mm_P5.08mm_Horizontal
RaspberryPI5GPIO1: Conn_02x20_Odd_Even; RHDR40W60P250_2X20_5100X500X23
U1: AO4805; SOIC127P600X175-8N

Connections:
+12V: J1.3, J1.4, J3.1, R9.2, R10.2, U1.1 (S2), U1.3 (S1)
/Blue LED ChC: J3.4, Q3.2 (D)
/Far Red LED ChA: J3.2, Q1.2 (D)
/GPIO12: J2.3, R6.1
/GPIO13: J2.2, R5.1
/GPIO19: J2.1, R4.1
/GPIO23: J2.4, R7.1, RaspberryPI5GPIO1.18
/GPIO24: J2.5, R8.2, RaspberryPI5GPIO1.16
/LED CH3: J4.1, U1.7 (D2), U1.8 (D2)
/LED CH4 (PWM): J4.2, U1.5 (D1), U1.6 (D1)
/Red LED ChB: J3.3, Q2.2 (D)
GND: J1.1, J1.2, J2.6, J4.3, J9.2, Q1.3 (S), Q2.3 (S), Q3.3 (S), Q4.1 (E), Q5.1 (E), R1.2, R2.2, R3.2, RaspberryPI5GPIO1.6, RaspberryPI5GPIO1.9, RaspberryPI5GPIO1.14, RaspberryPI5GPIO1.20, RaspberryPI5GPIO1.25, RaspberryPI5GPIO1.30, RaspberryPI5GPIO1.34, RaspberryPI5GPIO1.39
unnamed: J9.1, RaspberryPI5GPIO1.2, RaspberryPI5GPIO1.4
unnamed: Q1.1 (G), R1.1, R4.2
unnamed: Q2.1 (G), R2.1, R5.2
unnamed: Q3.1 (G), R3.1, R6.2
unnamed: Q4.2 (B), R7.2
unnamed: Q4.3 (C), R9.1, U1.2 (G2)
unnamed: Q5.2 (B), R8.1
unnamed: Q5.3 (C), R10.1, U1.4 (G1)
unnamed: RaspberryPI5GPIO1.1, RaspberryPI5GPIO1.17

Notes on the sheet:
Connect to Touchdisplay 2 J1
RPI pin 16
RPI pin 33
PWM X
Black
Blue LED
RPI pin 18
21 mm 24 AWG
RPI pin 35
RPI pin 32
Red LED
MOLEX PICO BLADE 2-PIN CABLE - 2
RPI pin 14
Far Red LED
Green LED
Red
GPIO12 (pin 32), GPIO13 (pin33), GPIO19 (pin35) control the Blue, RED and Far Red LEDs, respectively via the 3 channel MOSFET ILRZ44N circuit.

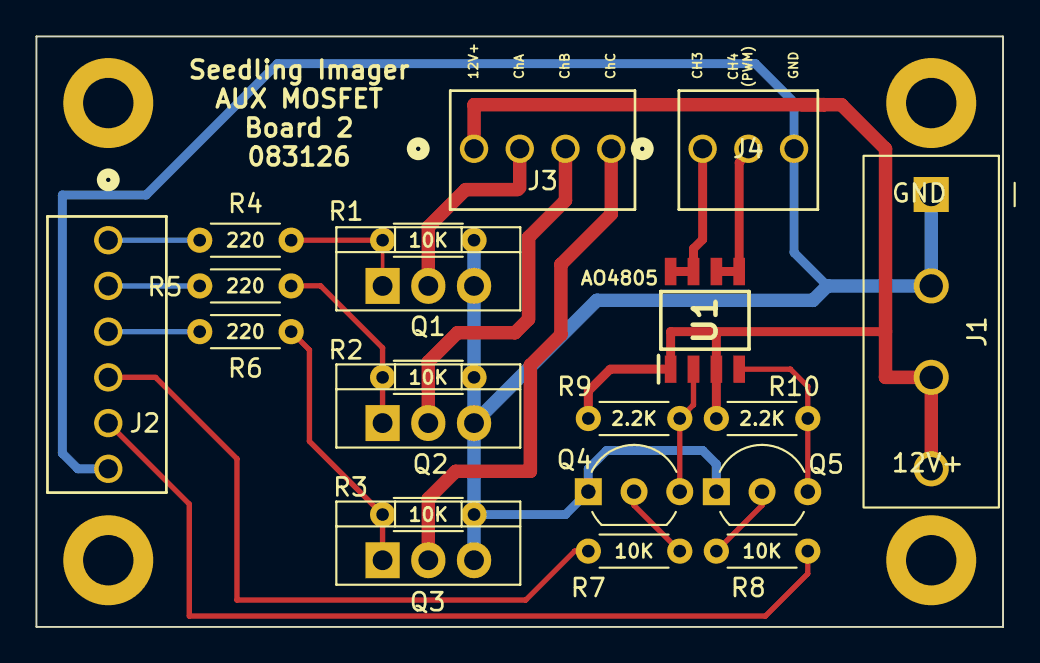
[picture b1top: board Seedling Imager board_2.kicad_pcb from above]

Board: 2 copper layers, 53.7 x 32.8 mm, 21 parts (0 on the bottom side), 19 nets.

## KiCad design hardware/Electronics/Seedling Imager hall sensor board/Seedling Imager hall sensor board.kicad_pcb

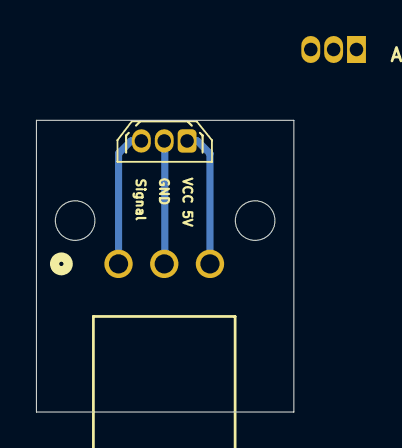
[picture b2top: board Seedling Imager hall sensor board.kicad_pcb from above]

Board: 2 copper layers, 14.3 x 16.2 mm, 5 parts (0 on the bottom side), 3 nets.

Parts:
A3144: A1104xLH; TO-92L_Inline
H1, H2: MountingHole; MountingHole_2.2mm_M2
J1: 22053031; CONN_A-7478-03A_MOL
U1: A3144; TO-92Flat

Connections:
/GND: J1.2, U1.2 (GND)
/Signal: J1.1, U1.3 (SIGNAL)
/VCC 5V: J1.3, U1.1 (V_{CC})

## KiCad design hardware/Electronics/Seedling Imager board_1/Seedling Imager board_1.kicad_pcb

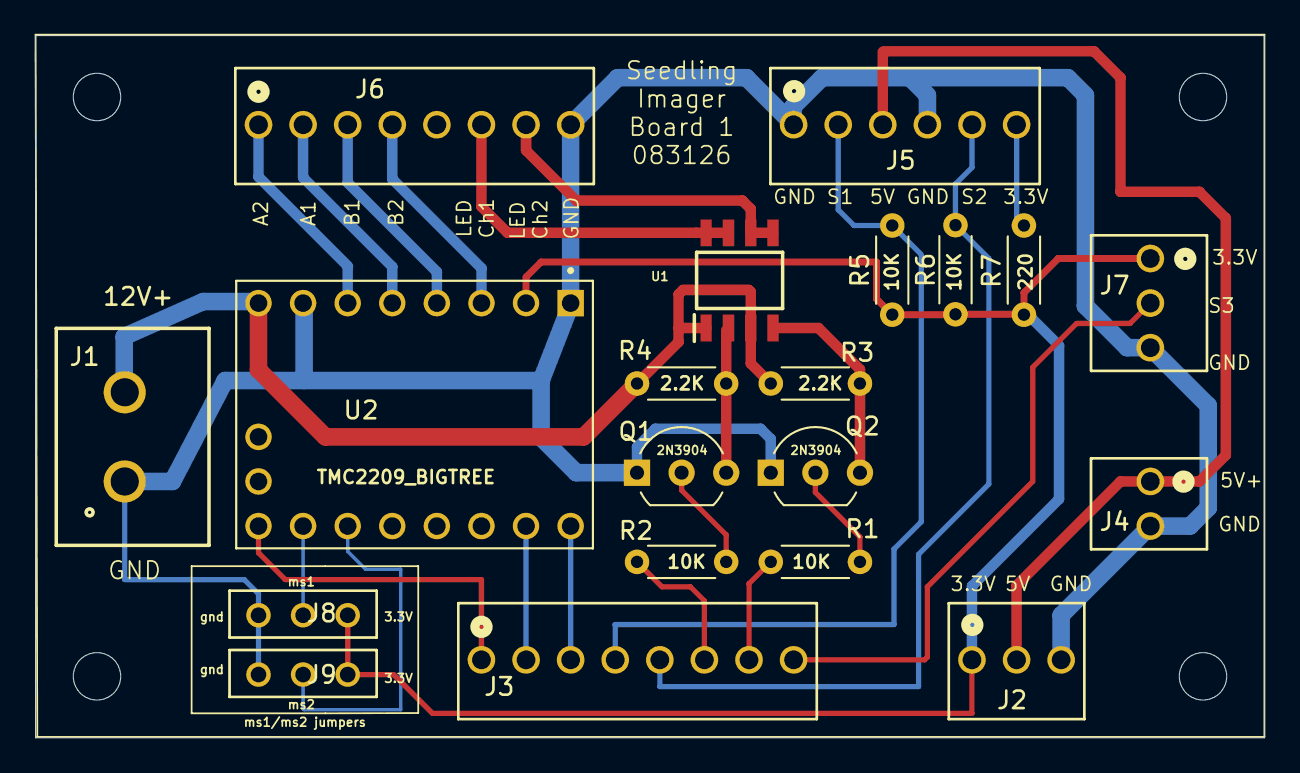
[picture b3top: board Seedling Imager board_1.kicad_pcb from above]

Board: 2 copper layers, 70.0 x 40.0 mm, 24 parts (0 on the bottom side), 25 nets.

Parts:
H1, H2, H3, H4: MountingHole; MountingHole_2.7mm
J1: 691313510002; 691311500102
J2, J7: 22112032; CONN_A-6373-03A_MOL
J3, J6: 22112082; CONN_A-6373-08A_MOL
J4: 22112022; CONN_A-6373-02A_MOL
J5: 22112062; CONN_A-6373-06A_MOL
J8, J9: Conn_01x03_Pin; CON3_1X3_TU_TSW
Q1, Q2: 2N3904; TO-92_Inline_Wide
R1, R2, R5, R6: 10K; R_Axial_DIN0204_L3.6mm_D1.6mm_P5.08mm_Horizontal
R3, R4: 2.2K; R_Axial_DIN0204_L3.6mm_D1.6mm_P5.08mm_Horizontal
R7: 220; R_Axial_DIN0204_L3.6mm_D1.6mm_P5.08mm_Horizontal
U1: SOIC127P600X175-8N
U2: TMC2209_BIGTREE; MODULE_TMC2209_BigTreeTech

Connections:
+3.3V (GPIO pin 1): J2.1, J7.1, J8.3, J9.3, R5.2, R6.2, R7.2, U2.2 (VIO)
+5V: J2.2, J4.1, J5.3
+12V: J1.2, R3.1, R4.1, U1.1 (S2), U1.3 (S1), U2.8 (VM)
/black: J6.1, U2.6 (M2A)
/blue: J6.4, U2.3 (M2B)
/green: J6.2, U2.5 (M1A)
/ms1: J8.2, U2.10 (MS1)
/ms2: J9.2, U2.11 (MS2)
/red: J6.3, U2.4 (M1B)
GND: J1.1, J2.3, J4.2, J5.1, J5.4, J6.8, J7.3, J8.1, J9.1, Q1.1 (E), Q2.1 (E), U2.1 (GND), U2.7 (GND)
GPIO6 pin31: J3.8, J7.2
unnamed: J6.6, U1.7 (D2), U1.8 (D2)
unnamed: J6.7, U1.5 (D1), U1.6 (D1)
unnamed: Q1.2 (B), R2.2
unnamed: Q1.3 (C), R4.2, U1.2 (G2)
unnamed: Q2.2 (B), R1.2
unnamed: Q2.3 (C), R3.2, U1.4 (G1)
RPI GPIO16 pin 36: J3.3, U2.16 (DIR)
RPI GPIO17 pin 11: J3.7, R1.1
RPI GPIO20 pin 38: J3.2, U2.15 (STEP)
RPI GPIO21 pin 40: J3.1, U2.9 (~EN)
RPI GPIO22 pin 15 (optical RCV): J3.5, J5.5, R6.1
RPI GPIO26 pin 37 (hall effect): J3.4, J5.2, R5.1
RPI GPIO27 pin 13: J3.6, R2.1
optical TM 3V: J5.6, R7.1

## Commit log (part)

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2026-02-11 display2: initial import
2026-04-15 v0.07: dual IR illumination, tabbed Camera Config, fixed preview snapshot timing, GT2 belt homing
2026-06-01 Feat: per-plate optical W measurement, 6-sensor bracket centering, registration logging
2026-06-17 Add CERN Open Hardware Licence Version 2 text
    This file contains the full text of the CERN Open Hardware Licence Version 2 - Strongly Reciprocal, outlining the terms for using, modifying, and distributing hardware designs.
2026-06-17 Create NOTICE.txt for Open Hardware licensing
    Add copyright notice and licensing information for Open Hardware documentation.
2026-06-17 Create README for Seedling Imager hardware design
    Added README.md for Seedling Imager hardware design, detailing assembly, components, and licensing.
2026-06-17 Update BOM file name and citation DOI in README
2026-06-24 Create CAD files
    Fusion 360 CAD files of subassemblies
2026-06-24 Add README for Dual Bearing Belt Drive subassembly
2026-06-24 dual bearing drive subassembly
2026-06-24 Add image placeholder to README for belt drive
2026-06-24 Create Drive Plate
2026-06-24 Replace image placeholder with actual image link
    Updated image reference for Dual Bearing Belt Drive.
2026-06-24 Fusion 360 dual bearing belt drive subassembly components
